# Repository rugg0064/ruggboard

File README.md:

# ruggboard

My open source full sized keyboard. Practice demo projects included too.

# Primary features

* Single push button rotary encoder
* 107 Key
* Hot swap sockets
* North facing key mounts
* Addressable reverse mount RGB keys
* USB C Hub
* Integrated plate mount

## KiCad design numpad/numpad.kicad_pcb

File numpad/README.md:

# Numpad

First, I am starting with a numpad that has most of the features I want

## Features

* Single push button rotary encoder
* Regular numpad with 3 top keys
* Hot swap sockets
* North facing key mounts
* Addressable reverse mount RGB keys
* Integrated plate mount

Essentially, the full size design without the usb hub.

## Libraries

* https://github.com/keebio/Keebio-Parts.pretty
* https://github.com/keebio/keebio-components

## Products

### Microcontroller

https://keeb.io/products/rp2040-pro-micro-usb-c-controller

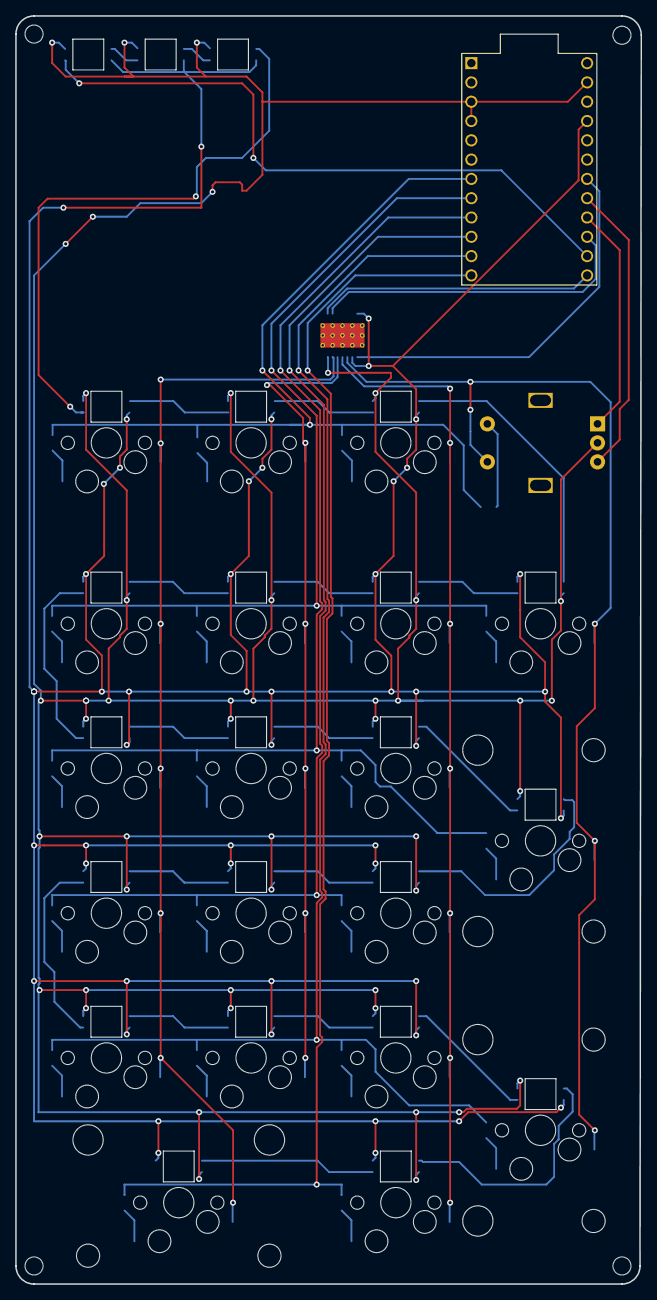
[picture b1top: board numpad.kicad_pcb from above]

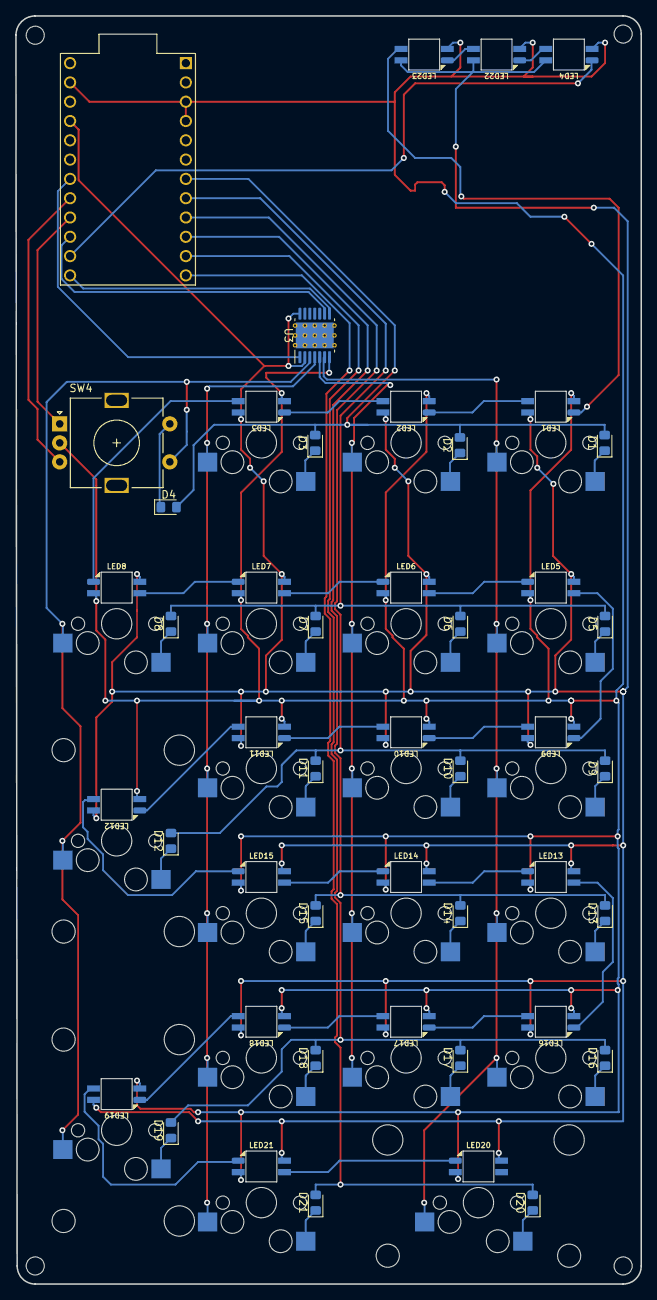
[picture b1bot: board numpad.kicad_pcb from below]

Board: 2 copper layers, 82.3 x 166.9 mm, 67 parts (23 on the bottom side), 61 nets.

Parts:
D1, D2, D3, D4, D5, D6, D7, D8, D9, D10, D11, D12, D13, D14, D15, D16, D17, D18, D19, D20, D21: DIODE; D_0805_2012Metric_Pad1.15x1.40mm_HandSolder
LED1, LED2, LED3, LED4, LED5, LED6, LED7, LED8, LED9, LED10, LED11, LED12, LED13, LED14, LED15, LED16, LED17, LED18, LED19, LED20, LED21, LED22, LED23: SK6812MINI-E; SK6812-MINI-E-Reverse
SW1, SW2, SW3, SW5, SW6, SW7, SW8, SW9, SW10, SW11, SW13, SW14, SW15, SW16, SW17, SW18, SW21: SW_SPST; MXOnly-1U-Hotswap
SW4: RotaryEncoder_Switch; RotaryEncoder_Alps_EC11E-Switch_Vertical_H20mm
SW12, SW19: SW_SPST; MXOnly-2U-Hotswap-VerticalStabilizers
SW20: SW_SPST; MXOnly-2U-Hotswap
U1: ProMicro
U3: 74HC164; HTSSOP-14-1EP_4.4x5mm_P0.65mm_EP3.4x5mm_Mask3x3.1mm_Thermal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

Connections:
+5V: LED1.2 (VDD), LED2.2 (VDD), LED3.2 (VDD), LED4.2 (VDD), LED5.2 (VDD), LED6.2 (VDD), LED7.2 (VDD), LED8.2 (VDD), LED9.2 (VDD), LED10.2 (VDD), LED11.2 (VDD), LED12.2 (VDD), LED13.2 (VDD), LED14.2 (VDD), LED15.2 (VDD), LED16.2 (VDD), LED17.2 (VDD), LED18.2 (VDD), LED19.2 (VDD), LED20.2 (VDD), LED21.2 (VDD), LED22.2 (VDD), LED23.2 (VDD), U1.21 (VCC), U3.2 (DSB), U3.14 (VCC)
/COL1: SW1.1 (A), SW5.1 (A), SW9.1 (A), SW13.1 (A), SW16.1 (A), SW20.1 (A), U3.6 (Q3)
/COL2: SW2.1 (A), SW6.1 (A), SW10.1 (A), SW14.1 (A), SW17.1 (A), U3.5 (Q2)
/COL3: SW3.1 (A), SW7.1 (A), SW11.1 (A), SW15.1 (A), SW18.1 (A), SW21.1 (A), U3.4 (Q1)
/COL4: SW4.S1, SW8.1 (A), SW12.1 (A), SW19.1 (A), U3.3 (Q0)
/COLCLOCK: U1.13 (B6), U3.8 (CP)
/COLSET: U1.15 (B3), U3.9 (~MR)
/ENCODER_A: SW4.B, U1.17 (F7)
/ENCODER_B: SW4.A, U1.16 (B1)
/LED_DATA: LED4.3 (DIN), U1.14 (B2)
/ROW1: D1.2 (A), D2.2 (A), D3.2 (A), D4.2 (A), U1.7 (D4)
/ROW2: D5.2 (A), D6.2 (A), D7.2 (A), D8.2 (A), U1.8 (C6)
/ROW3: D9.2 (A), D10.2 (A), D11.2 (A), D12.2 (A), U1.9 (D7)
/ROW4: D13.2 (A), D14.2 (A), D15.2 (A), U1.10 (E6)
/ROW5: D16.2 (A), D17.2 (A), D18.2 (A), D19.2 (A), U1.11 (B4)
/ROW6: D20.2 (A), D21.2 (A), U1.12 (B5)
/SHIFTREGIN: U1.18 (F6), U3.1 (DSA)
GND: LED1.4 (GND), LED2.4 (GND), LED3.4 (GND), LED4.4 (GND), LED5.4 (GND), LED6.4 (GND), LED7.4 (GND), LED8.4 (GND), LED9.4 (GND), LED10.4 (GND), LED11.4 (GND), LED12.4 (GND), LED13.4 (GND), LED14.4 (GND), LED15.4 (GND), LED16.4 (GND), LED17.4 (GND), LED18.4 (GND), LED19.4 (GND), LED20.4 (GND), LED21.4 (GND), LED22.4 (GND), LED23.4 (GND), SW4.C, U1.3 (GND), U1.4 (GND), U1.23 (GND), U3.7 (GND)
unnamed: D1.1 (K), SW1.2 (B)
unnamed: D2.1 (K), SW2.2 (B)
unnamed: D3.1 (K), SW3.2 (B)
unnamed: D4.1 (K), SW4.S2
unnamed: D5.1 (K), SW5.2 (B)
unnamed: D6.1 (K), SW6.2 (B)
unnamed: D7.1 (K), SW7.2 (B)
unnamed: D8.1 (K), SW8.2 (B)
unnamed: D9.1 (K), SW9.2 (B)
unnamed: D10.1 (K), SW10.2 (B)
unnamed: D11.1 (K), SW11.2 (B)
unnamed: D12.1 (K), SW12.2 (B)
unnamed: D13.1 (K), SW13.2 (B)
unnamed: D14.1 (K), SW14.2 (B)
unnamed: D15.1 (K), SW15.2 (B)
unnamed: D16.1 (K), SW16.2 (B)
unnamed: D17.1 (K), SW17.2 (B)
unnamed: D18.1 (K), SW18.2 (B)
unnamed: D19.1 (K), SW19.2 (B)
unnamed: D20.1 (K), SW20.2 (B)
unnamed: D21.1 (K), SW21.2 (B)
unnamed: LED1.1 (DOUT), LED2.3 (DIN)
unnamed: LED1.3 (DIN), LED23.1 (DOUT)
unnamed: LED2.1 (DOUT), LED3.3 (DIN)
unnamed: LED3.1 (DOUT), LED8.3 (DIN)
unnamed: LED5.1 (DOUT), LED9.3 (DIN)
unnamed: LED5.3 (DIN), LED6.1 (DOUT)
unnamed: LED6.3 (DIN), LED7.1 (DOUT)
unnamed: LED7.3 (DIN), LED8.1 (DOUT)
unnamed: LED10.1 (DOUT), LED11.3 (DIN)
unnamed: LED9.1 (DOUT), LED10.3 (DIN)
unnamed: LED11.1 (DOUT), LED12.3 (DIN)
unnamed: LED12.1 (DOUT), LED15.3 (DIN)
unnamed: LED13.1 (DOUT), LED16.3 (DIN)
unnamed: LED13.3 (DIN), LED14.1 (DOUT)
unnamed: LED14.3 (DIN), LED15.1 (DOUT)
unnamed: LED16.1 (DOUT), LED17.3 (DIN)
unnamed: LED17.1 (DOUT), LED18.3 (DIN)
unnamed: LED18.1 (DOUT), LED19.3 (DIN)
unnamed: LED19.1 (DOUT), LED21.3 (DIN)
unnamed: LED20.3 (DIN), LED21.1 (DOUT)
unnamed: LED22.1 (DOUT), LED23.3 (DIN)
unnamed: LED4.1 (DOUT), LED22.3 (DIN)

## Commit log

2024-05-02 Pull test numpad into project
